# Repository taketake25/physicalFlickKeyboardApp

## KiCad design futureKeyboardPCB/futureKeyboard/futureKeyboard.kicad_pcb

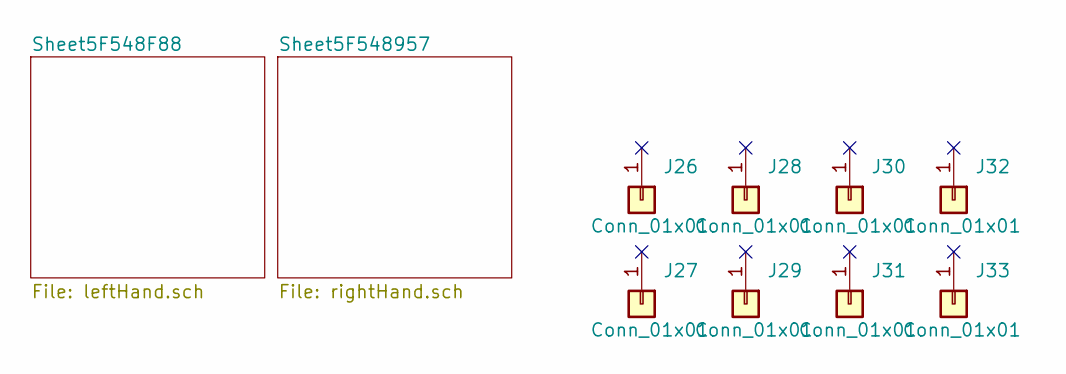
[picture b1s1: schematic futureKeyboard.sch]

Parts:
J26, J27, J28, J29, J30, J31, J32, J33: Conn_01x01; HOLE_3.2mm_nopad

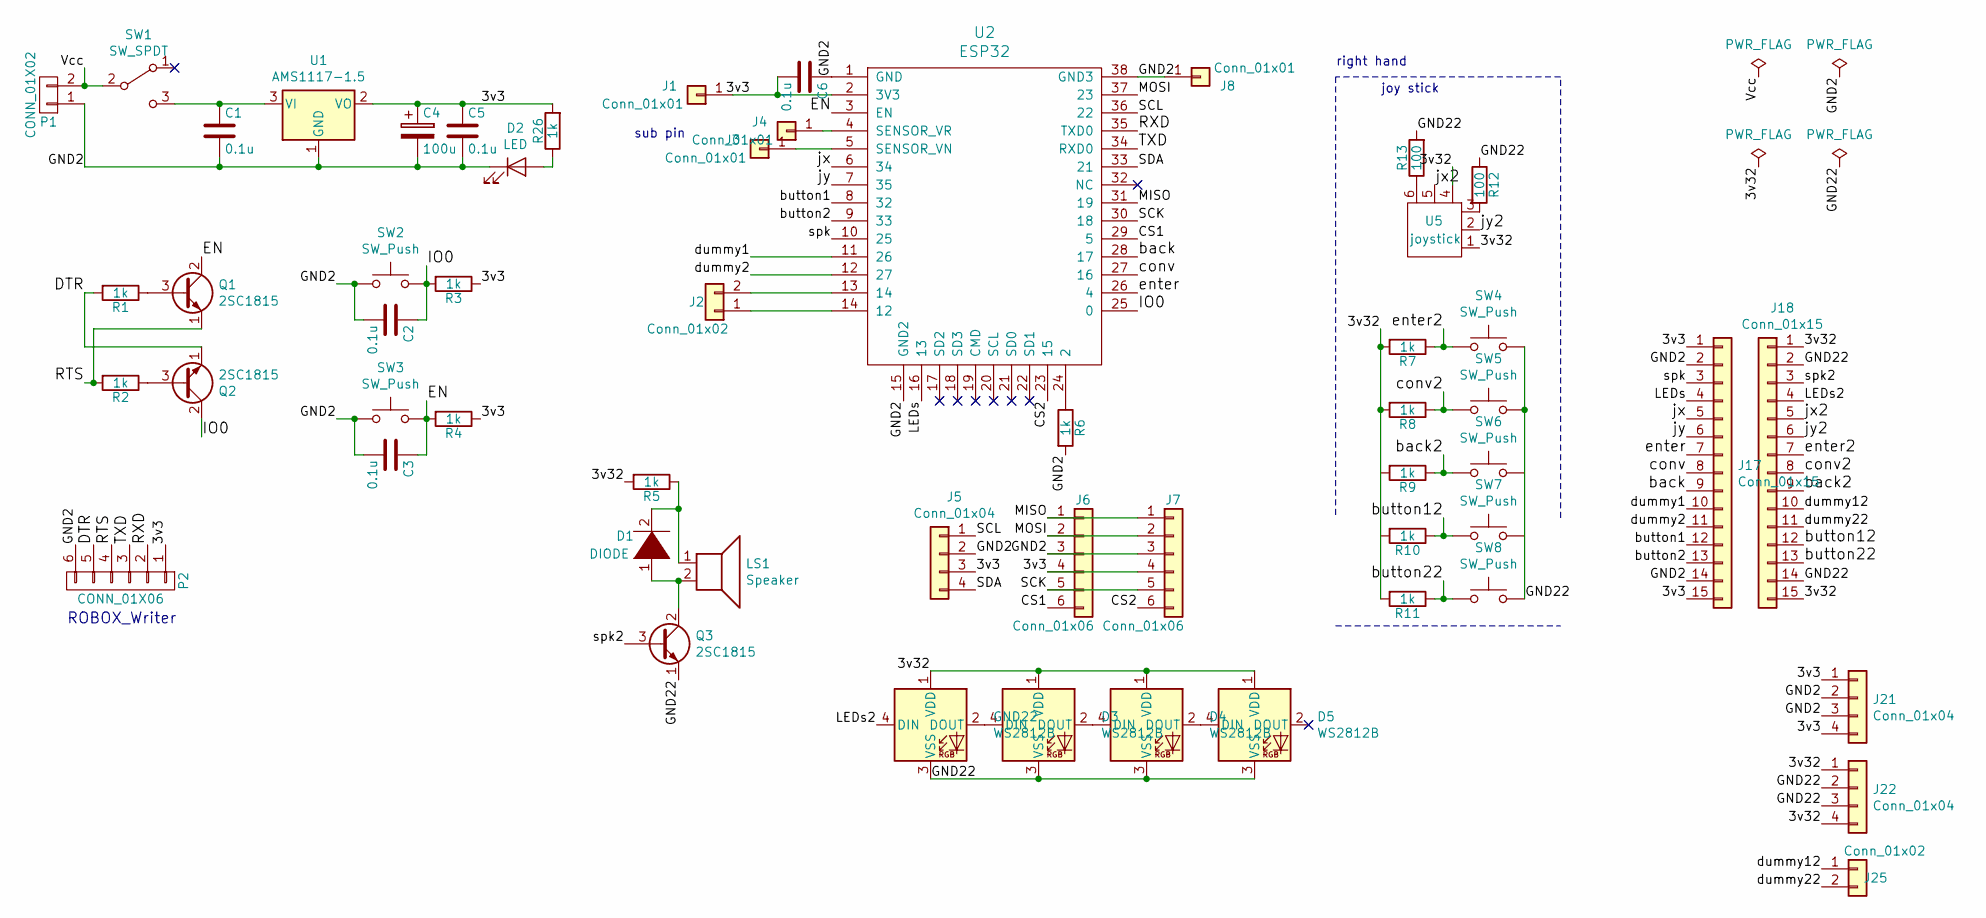
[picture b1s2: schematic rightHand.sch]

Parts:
C1, C2, C3, C5, C6: 0.1u; SMD-1608
C4: 100u; CP_Radial_D4.0mm_P2.00mm
D1: DIODE; D_A-405_P7.62mm_Horizontal
D2: LED; 2012LED
D3, D4, D5: WS2812B
GND22: WS2812B
J1, J3, J4, J8: Conn_01x01; PinHeader_1x01_P2.54mm_Vertical
J2, J25: Conn_01x02; PinHeader_1x02_P2.54mm_Vertical
J5: Conn_01x04; PinHeader_1x04_P2.54mm_Vertical
J6, J7: Conn_01x06; PinHeader_1x06_P2.54mm_Vertical
J17, J18: Conn_01x15; PinHeader_1x15_P2.54mm_Vertical_SMD_Pin1Left
J21, J22: Conn_01x04; PinHeader_1x04_P2.54mm_Vertical_SMD_Pin1Left
LS1: Speaker; small_speaker
P1: CONN_01X02; Connector_EH_2pin
P2: CONN_01X06; PinHeader_1x06_P2.54mm_Horizontal
Q1, Q2, Q3: 2SC1815; TO-92_Inline
R1, R2, R3, R4, R5, R6, R7, R8, R9, R10, R11, R26: 1k; SMD-1608
R12, R13: 100; SMD-1608
SW1: SW_SPDT; PinHeader_1x03_P2.54mm_Vertical
SW2, SW3, SW7, SW8: SW_Push; SMD_SW
SW4, SW5, SW6: SW_Push; SW_Cherry_MX_1.00u_PCB
U1: AMS1117-1.5; SOT-223-3_TabPin2
U2: ESP32; ESP-WROOM-32
U5: joystick; joyStick

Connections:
/Sheet5F548957/3v3: C4.1, C5.1, C6.2, J1.1, J5.3, J6.4, J7.4, J17.1, J17.15, J21.1, J21.4, P2.1, R3.1, R4.1, R26.2, U1.2 (VO), U2.2 (3V3)
/Sheet5F548957/3v32: D3.1 (VDD), D4.1 (VDD), D5.1 (VDD), GND22.1 (VDD), J18.1, J18.15, J22.1, J22.4, R5.2, R7.2, R8.2, R9.2, R10.2, R11.2, U5.1, U5.4
/Sheet5F548957/CS1: J6.6, U2.29 (5)
/Sheet5F548957/CS2: J7.6, U2.23 (15)
/Sheet5F548957/DTR: P2.5, Q2.1 (E), R1.2
/Sheet5F548957/EN: C3.1, Q1.2 (C), R4.2, SW3.2, U2.3 (EN)
/Sheet5F548957/GND2: C1.2, C2.2, C3.2, C4.2, C5.2, C6.1, D2.1 (K), J5.2, J6.3, J7.3, J8.1, J17.2, J17.14, J21.2, J21.3, P1.1, P2.6, R6.2, SW2.1, SW3.1, U1.1 (GND), U2.1 (GND), U2.15 (GND2), U2.38 (GND3)
/Sheet5F548957/GND22: D3.3 (VSS), D4.3 (VSS), D5.3 (VSS), GND22.3 (VSS), J18.2, J18.14, J22.2, J22.3, Q3.1 (E), R12.1, R13.2, SW4.2, SW5.2, SW6.2, SW7.2, SW8.2
/Sheet5F548957/IO0: C2.1, Q2.2 (C), R3.2, SW2.2, U2.25 (0)
/Sheet5F548957/LEDs: J17.4, U2.16 (13)
/Sheet5F548957/LEDs2: GND22.4 (DIN), J18.4
/Sheet5F548957/MISO: J6.1, J7.1, U2.31 (19)
/Sheet5F548957/MOSI: J6.2, J7.2, U2.37 (23)
/Sheet5F548957/RTS: P2.4, Q1.1 (E), R2.2
/Sheet5F548957/RXD: P2.2, U2.35 (TXD0)
/Sheet5F548957/SCK: J6.5, J7.5, U2.30 (18)
/Sheet5F548957/SCL: J5.1, U2.36 (22)
/Sheet5F548957/SDA: J5.4, U2.33 (21)
/Sheet5F548957/TXD: P2.3, U2.34 (RXD0)
/Sheet5F548957/Vcc: P1.2, SW1.2 (B)
/Sheet5F548957/back: J17.9, U2.28 (17)
/Sheet5F548957/back2: J18.9, R9.1, SW6.1
/Sheet5F548957/button1: J17.12, U2.8 (32)
/Sheet5F548957/button2: J17.13, U2.9 (33)
/Sheet5F548957/button12: J18.12, R10.1, SW7.1
/Sheet5F548957/button22: J18.13, R11.1, SW8.1
/Sheet5F548957/conv: J17.8, U2.27 (16)
/Sheet5F548957/conv2: J18.8, R8.1, SW5.1
/Sheet5F548957/dummy1: J17.10, U2.11 (26)
/Sheet5F548957/dummy2: J17.11, U2.12 (27)
/Sheet5F548957/dummy12: J18.10, J25.1
/Sheet5F548957/dummy22: J18.11, J25.2
/Sheet5F548957/enter: J17.7, U2.26 (4)
/Sheet5F548957/enter2: J18.7, R7.1, SW4.1
/Sheet5F548957/jx: J17.5, U2.6 (34)
/Sheet5F548957/jx2: J18.5, U5.5
/Sheet5F548957/jy: J17.6, U2.7 (35)
/Sheet5F548957/jy2: J18.6, U5.2
/Sheet5F548957/spk: J17.3, U2.10 (25)
/Sheet5F548957/spk2: J18.3, Q3.3 (B)
unnamed: C1.1, SW1.3 (C), U1.3 (VI)
unnamed: D1.1 (K), LS1.2, Q3.2 (C)
unnamed: D1.2 (A), LS1.1, R5.1
unnamed: D2.2 (A), R26.1
unnamed: D3.2 (DOUT), D4.4 (DIN)
unnamed: D3.4 (DIN), GND22.2 (DOUT)
unnamed: D4.2 (DOUT), D5.4 (DIN)
unnamed: J2.1, U2.14 (12)
unnamed: J2.2, U2.13 (14)
unnamed: J3.1, U2.5 (SENSOR_VN)
unnamed: J4.1, U2.4 (SENSOR_VR)
unnamed: Q1.3 (B), R1.1
unnamed: Q2.3 (B), R2.1
unnamed: R6.1, U2.24 (2)
unnamed: R12.2, U5.3
unnamed: R13.1, U5.6

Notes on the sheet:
joy stick
right hand
ROBOX_Writer
sub pin

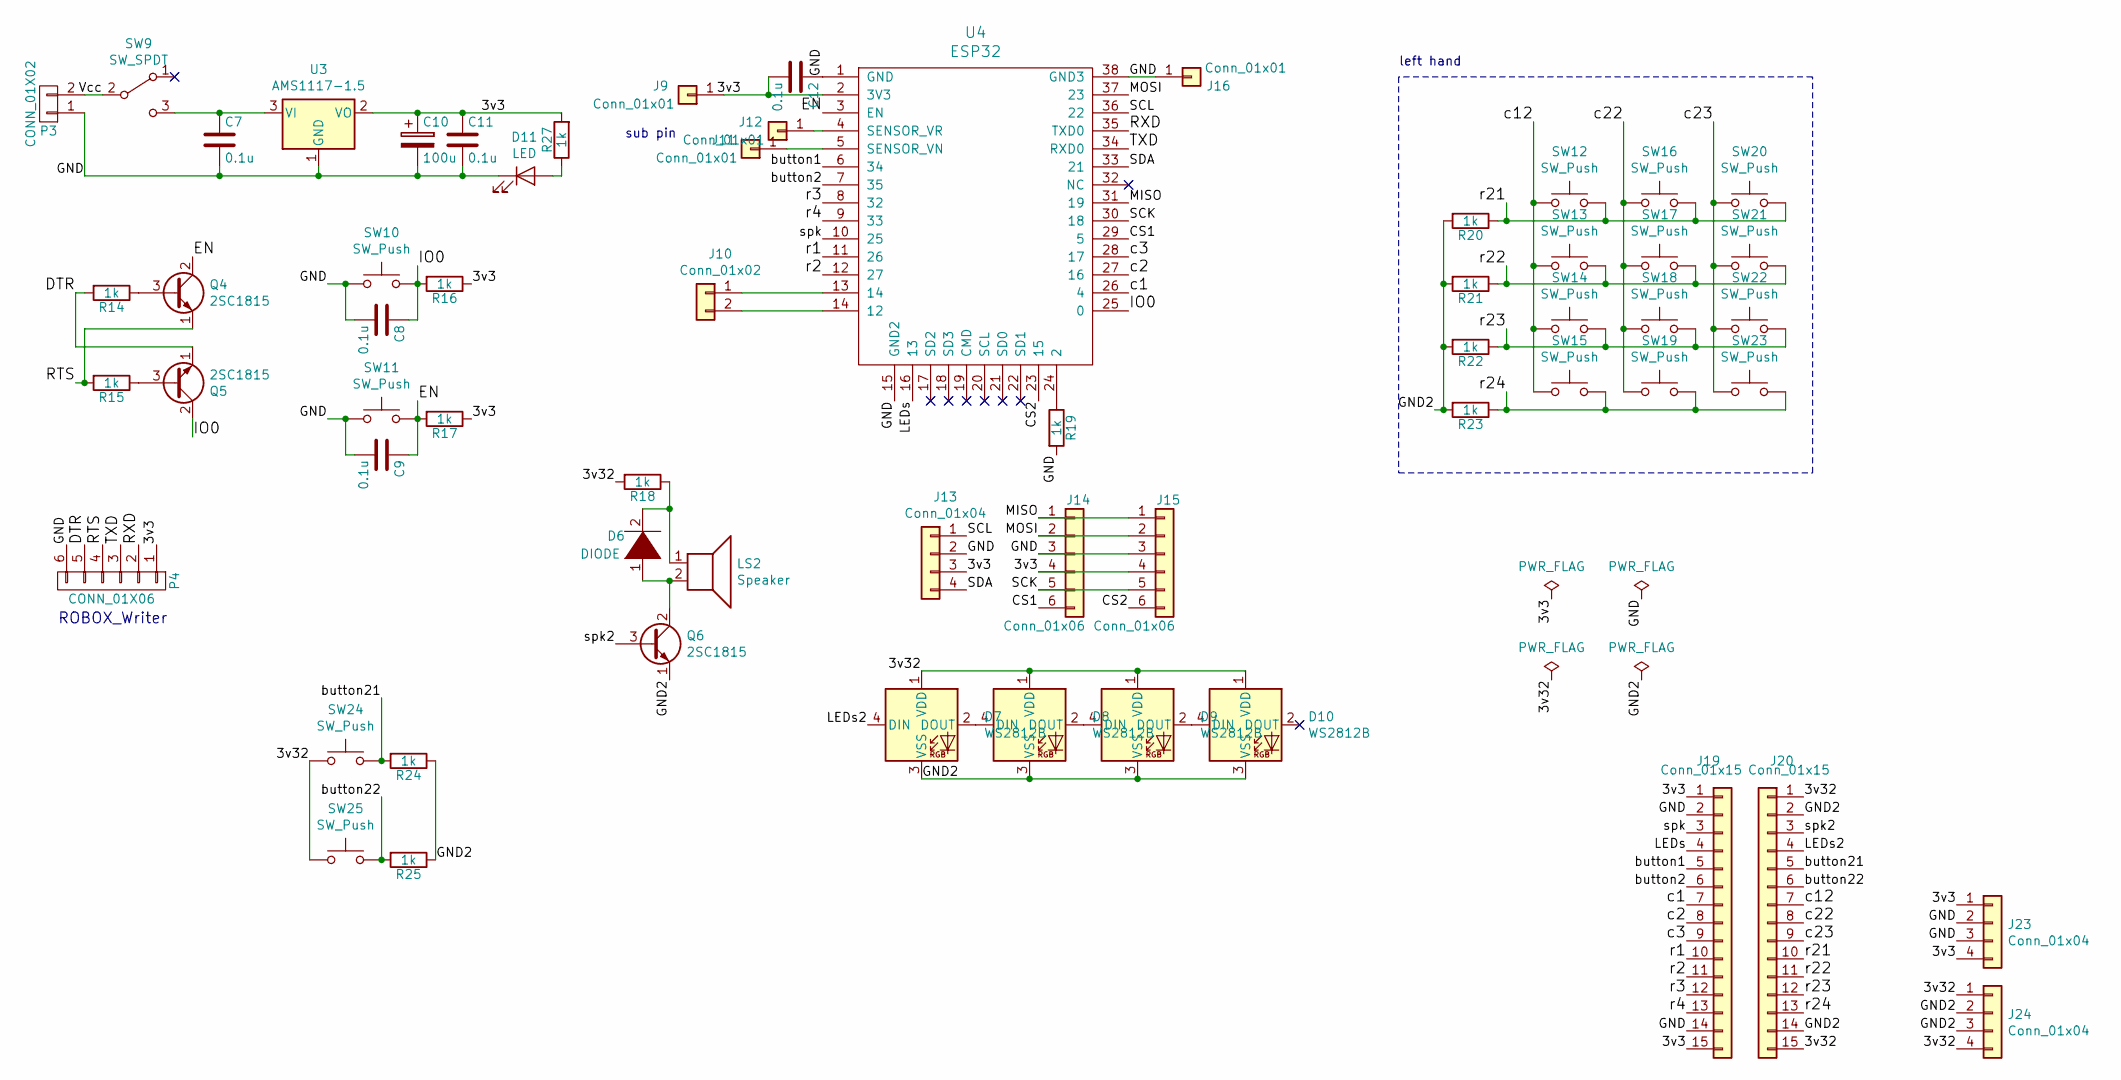
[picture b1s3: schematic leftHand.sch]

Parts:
C7, C8, C9, C11, C12: 0.1u; SMD-1608
C10: 100u; CP_Radial_D4.0mm_P2.00mm
D6: DIODE; D_A-405_P7.62mm_Horizontal
D7, D8, D9, D10: WS2812B
D11: LED; 2012LED
J9, J11, J12, J16: Conn_01x01; PinHeader_1x01_P2.54mm_Vertical
J10: Conn_01x02; PinHeader_1x02_P2.54mm_Vertical
J13: Conn_01x04; PinHeader_1x04_P2.54mm_Vertical
J14, J15: Conn_01x06; PinHeader_1x06_P2.54mm_Vertical
J19, J20: Conn_01x15; PinHeader_1x15_P2.54mm_Vertical_SMD_Pin1Left
J23, J24: Conn_01x04; PinHeader_1x04_P2.54mm_Vertical_SMD_Pin1Left
LS2: Speaker; small_speaker
P3: CONN_01X02; Connector_EH_2pin
P4: CONN_01X06; PinHeader_1x06_P2.54mm_Horizontal
Q4, Q5, Q6: 2SC1815; TO-92_Inline
R14, R15, R16, R17, R18, R19, R20, R21, R22, R23, R24, R25, R27: 1k; SMD-1608
SW9: SW_SPDT; PinHeader_1x03_P2.54mm_Vertical
SW10, SW11, SW24, SW25: SW_Push; SMD_SW
SW12, SW13, SW14, SW15, SW16, SW17, SW18, SW19, SW20, SW21, SW22, SW23: SW_Push; SW_Cherry_MX_1.00u_PCB
U3: AMS1117-1.5; SOT-223-3_TabPin2
U4: ESP32; ESP-WROOM-32

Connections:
/Sheet5F548F88/3v3: C10.1, C11.1, C12.2, J9.1, J13.3, J14.4, J15.4, J19.1, J19.15, J23.1, J23.4, P4.1, R16.1, R17.1, R27.2, U3.2 (VO), U4.2 (3V3)
/Sheet5F548F88/3v32: D7.1 (VDD), D8.1 (VDD), D9.1 (VDD), D10.1 (VDD), J20.1, J20.15, J24.1, J24.4, R18.2, SW24.1, SW25.1
/Sheet5F548F88/CS1: J14.6, U4.29 (5)
/Sheet5F548F88/CS2: J15.6, U4.23 (15)
/Sheet5F548F88/DTR: P4.5, Q5.1 (E), R14.2
/Sheet5F548F88/EN: C9.1, Q4.2 (C), R17.2, SW11.2, U4.3 (EN)
/Sheet5F548F88/GND: C7.2, C8.2, C9.2, C10.2, C11.2, C12.1, D11.1 (K), J13.2, J14.3, J15.3, J16.1, J19.2, J19.14, J23.2, J23.3, P3.1, P4.6, R19.2, SW10.1, SW11.1, U3.1 (GND), U4.1 (GND), U4.15 (GND2), U4.38 (GND3)
/Sheet5F548F88/GND2: D7.3 (VSS), D8.3 (VSS), D9.3 (VSS), D10.3 (VSS), J20.2, J20.14, J24.2, J24.3, Q6.1 (E), R20.2, R21.2, R22.2, R23.2, R24.1, R25.1
/Sheet5F548F88/IO0: C8.1, Q5.2 (C), R16.2, SW10.2, U4.25 (0)
/Sheet5F548F88/LEDs: J19.4, U4.16 (13)
/Sheet5F548F88/LEDs2: D7.4 (DIN), J20.4
/Sheet5F548F88/MISO: J14.1, J15.1, U4.31 (19)
/Sheet5F548F88/MOSI: J14.2, J15.2, U4.37 (23)
/Sheet5F548F88/RTS: P4.4, Q4.1 (E), R15.2
/Sheet5F548F88/RXD: P4.2, U4.35 (TXD0)
/Sheet5F548F88/SCK: J14.5, J15.5, U4.30 (18)
/Sheet5F548F88/SCL: J13.1, U4.36 (22)
/Sheet5F548F88/SDA: J13.4, U4.33 (21)
/Sheet5F548F88/TXD: P4.3, U4.34 (RXD0)
/Sheet5F548F88/Vcc: P3.2, SW9.2 (B)
/Sheet5F548F88/button1: J19.5, U4.6 (34)
/Sheet5F548F88/button2: J19.6, U4.7 (35)
/Sheet5F548F88/button21: J20.5, R24.2, SW24.2
/Sheet5F548F88/button22: J20.6, R25.2, SW25.2
/Sheet5F548F88/c1: J19.7, U4.26 (4)
/Sheet5F548F88/c2: J19.8, U4.27 (16)
/Sheet5F548F88/c3: J19.9, U4.28 (17)
/Sheet5F548F88/c12: J20.7, SW12.1, SW13.1, SW14.1, SW15.1
/Sheet5F548F88/c22: J20.8, SW16.1, SW17.1, SW18.1, SW19.1
/Sheet5F548F88/c23: J20.9, SW20.1, SW21.1, SW22.1, SW23.1
/Sheet5F548F88/r1: J19.10, U4.11 (26)
/Sheet5F548F88/r2: J19.11, U4.12 (27)
/Sheet5F548F88/r3: J19.12, U4.8 (32)
/Sheet5F548F88/r4: J19.13, U4.9 (33)
/Sheet5F548F88/r21: J20.10, R20.1, SW12.2, SW16.2, SW20.2
/Sheet5F548F88/r22: J20.11, R21.1, SW13.2, SW17.2, SW21.2
/Sheet5F548F88/r23: J20.12, R22.1, SW14.2, SW18.2, SW22.2
/Sheet5F548F88/r24: J20.13, R23.1, SW15.2, SW19.2, SW23.2
/Sheet5F548F88/spk: J19.3, U4.10 (25)
/Sheet5F548F88/spk2: J20.3, Q6.3 (B)
unnamed: C7.1, SW9.3 (C), U3.3 (VI)
unnamed: D6.1 (K), LS2.2, Q6.2 (C)
unnamed: D6.2 (A), LS2.1, R18.1
unnamed: D7.2 (DOUT), D8.4 (DIN)
unnamed: D8.2 (DOUT), D9.4 (DIN)
unnamed: D9.2 (DOUT), D10.4 (DIN)
unnamed: D11.2 (A), R27.1
unnamed: J10.1, U4.13 (14)
unnamed: J10.2, U4.14 (12)
unnamed: J11.1, U4.5 (SENSOR_VN)
unnamed: J12.1, U4.4 (SENSOR_VR)
unnamed: Q4.3 (B), R14.1
unnamed: Q5.3 (B), R15.1
unnamed: R19.1, U4.24 (2)

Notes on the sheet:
left hand
ROBOX_Writer
sub pin

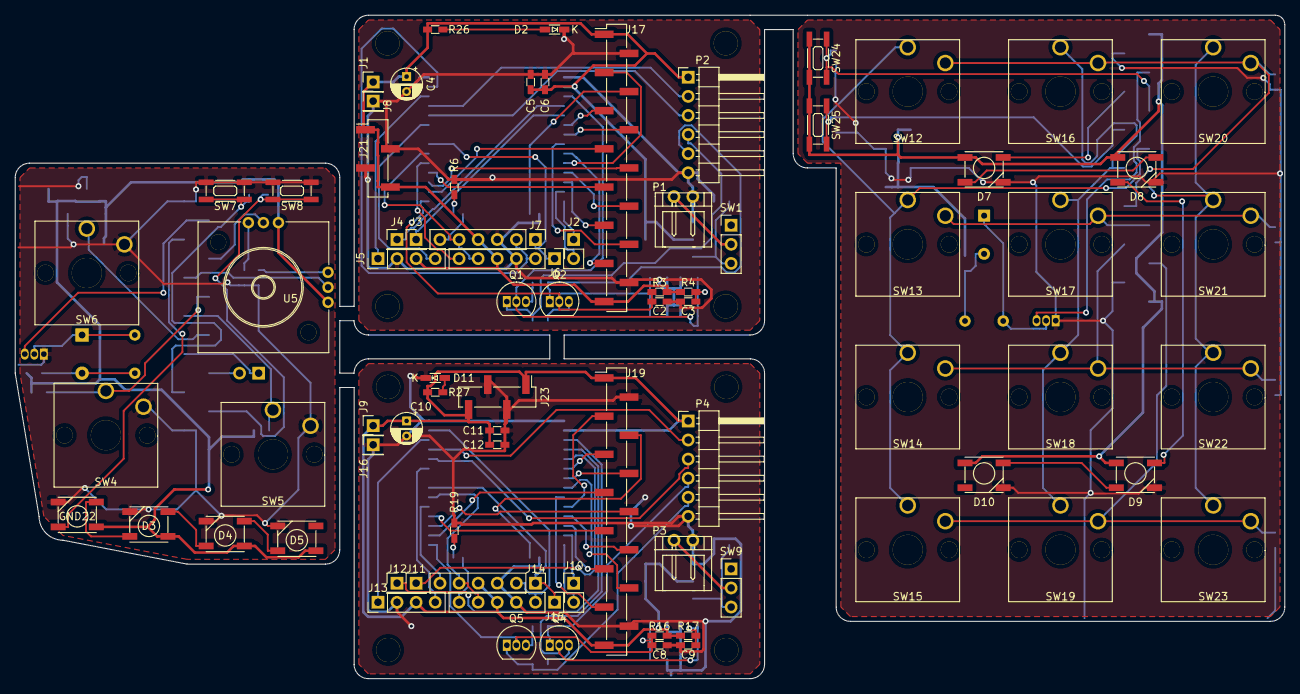
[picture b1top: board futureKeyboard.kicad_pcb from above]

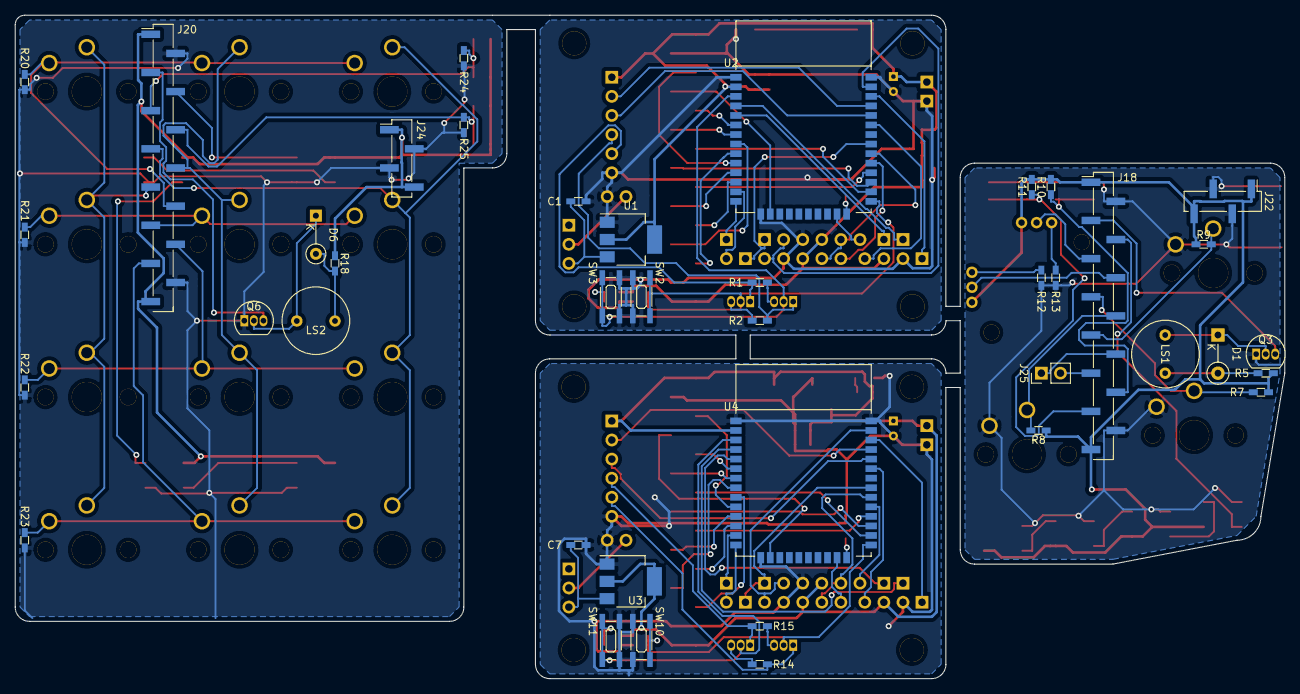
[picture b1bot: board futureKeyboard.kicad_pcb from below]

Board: 2 copper layers, 168.9 x 88.3 mm, 126 parts (40 on the bottom side), 110 nets.

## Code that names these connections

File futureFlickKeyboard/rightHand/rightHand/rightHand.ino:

#include <WiFi.h>
#include <esp_now.h>
#include <Adafruit_NeoPixel.h>
#include "BluetoothSerial.h"

#define LEDs 13
#define button1 32
#define button2 33
#define spk 25
#define enter 16
#define conv 17
#define back 4
#define jx 34
#define jy 35
#define pi 3.141592
#define CHANNEL 0

/* full color LED definition */
#ifdef __AVR__
#include <avr/power.h> // Required for 16 MHz Adafruit Trinket
#endif
#define NUMPIXELS 4 // Popular NeoPixel ring size
Adafruit_NeoPixel pixels(NUMPIXELS, LEDs, NEO_GRB + NEO_KHZ800);

BluetoothSerial SerialBT;

int lines[4]={0};
char w[2]={0};
char beforew[2]={0};
int key = 0;


// Init ESP Now with fallback
void InitESPNow() {
  WiFi.disconnect();
  if (esp_now_init() == ESP_OK) {
    Serial.println("ESPNow Init Success");
  }
  else {
    Serial.println("ESPNow Init Failed");
    ESP.restart();
  }
}

// config AP SSID
void configDeviceAP() {
  const char *SSID = "Slave_rightHand";
  bool result = WiFi.softAP(SSID, "ffkb_rightHand", CHANNEL, 0);
  if (!result) {
    Serial.println("AP Config failed.");
  } else {
    Serial.println("AP Config Success. Broadcasting with AP: " + String(SSID));
  }
}

// callback when data is recv from Master
void OnDataRecv(const uint8_t *mac_addr, const uint8_t *data, int data_len) {
  char macStr[18];
  snprintf(macStr, sizeof(macStr), "%02x:%02x:%02x:%02x:%02x:%02x",
           mac_addr[0], mac_addr[1], mac_addr[2], mac_addr[3], mac_addr[4], mac_addr[5]);
  Serial.print("Last Packet Recv from: "); Serial.println(macStr);
  Serial.print("Last Packet Recv Data: "); Serial.println(*data);
  Serial.println("");

  key = *data;
//  Serial.print("key:");

}


// ↑ ESP-NOW       ---------------------------------------------------------------------
// ↓ Original Code ---------------------------------------------------------------------


void setup() {
  Serial.begin(115200);
  SerialBT.begin("Future Flick Keyboard v0");

  pinMode(jx,INPUT); //ジョイスティック
  pinMode(jy,INPUT);
  pinMode(button1,INPUT);
  pinMode(button2,INPUT);
  pinMode(back,INPUT); // 消す
  pinMode(enter,INPUT); // 改行 or あ列
  pinMode(conv,INPUT); //スペース


  WiFi.mode(WIFI_AP);
  configDeviceAP();  // configure device AP mode
  Serial.print("AP MAC: "); Serial.println(WiFi.softAPmacAddress());  // This is the mac address of the Slave in AP Mode
  InitESPNow();  // Init ESPNow with a fallback logic
  esp_now_register_recv_cb(OnDataRecv);  // Once ESPNow is successfully Init, we will register for recv CB to get recv packer info.


  /* full color LED init */
  #if defined(__AVR_ATtiny85__) && (F_CPU == 16000000) // for setup full color LEDs
    clock_prescale_set(clock_div_1);
  #endif
  pixels.begin();
  pixels.clear(); // Set all pixel colors to 'off'
  pixels.setPixelColor(0, pixels.Color(255, 0, 0));
  pixels.setPixelColor(1, pixels.Color(0, 255, 0));
  pixels.setPixelColor(2, pixels.Color(0, 0, 255));
  pixels.setPixelColor(3, pixels.Color(255, 255, 255));
  pixels.show();
  delay(1000);
//  pixels.clear(); // Set all pixel colors to 'off'
//  pixels.show();


  w[0]=0; w[1]=0; // 入力内容を初期化  
  key=0;
}


void loop() {
  
  memset(lines,0,sizeof(lines[0])*4);
  //どのボタンが押されているかを認識し、keyに1~12の値として入力

//  Serial.print(digitalRead(enter));  Serial.print("  ");
//  Serial.print(analogRead(jx));  Serial.print("  ");
//  Serial.print(analogRead(jy));  Serial.println("  ");
  printKey(key);

  delay(50); 
}


void printKey(int key){ // 入力キーをinput
  int x = analogRead(jx); // ジョイスティックの値を取得（0~4095）
  int y = analogRead(jy);
  bool output = false;

  int wordIndex = 0;

  if(key!=0){ // 左手側が入力されているとき
    if(sqrt((x-2048)*(x-2048) + (y-2048)*(y-2048)) > 1250){ // ジョイスティックがある一定以上傾いていたとき（値の範囲に注意）
      float direc = (2.0*(atan2(2048-y,2048-x)+0.785398))/pi; // ジョイスティックの角度を求め、45度ごとに値が1ずつ変化するように変換（値の範囲に注意）

//      Serial.print(atan2(2048-y,2048-x)+0.785398);
      if(direc>=0){ // ジョイスティックの上側
        switch((int)direc){
          case 0:  Serial.print("<-"); w[1]='i'; wordIndex = 1; break; // ←
          case 1:  Serial.print("!"); w[1]='o'; wordIndex = 4; break; // ↓
          default:  Serial.print("->"); w[1]='e'; wordIndex = 3; break; // →
        }
        output = true;
      }else{ // ジョイスティックの下側（-1以上0未満の値がintにした際に0になっちゃうので）
        switch((int)direc){
          case -1: Serial.print("->"); w[1]='e'; wordIndex = 3; break; // →
          default: Serial.print("i"); w[1]='u'; wordIndex = 2; break; // ↑
        }
        output = true;
      }

    }else if(!digitalRead(enter)){ // フリックしない文字（あ行）はEnterキーで入力
      Serial.print("*");
      w[1]='a'; 
      wordIndex = 0; 
      output = true;
    }else{
      w[1]=0;
    }

    switch(key){
      case 1:w[0]=w[1];w[1]=0;break; //とりあえずESCを入力している
      case 2:w[0]='k';break;
      case 3:w[0]='s';break;
      case 4:w[0]='t';break;
      case 5:w[0]='n';break;
      case 6:w[0]='h';break;
      case 7:w[0]='m';break;
      case 8:w[0]='y';break;
      case 9:w[0]='r';break;
      case 10:w[0]=' ';break;
      case 11:w[0]='w';break;
      case 12:w[0]=' ';break;
    }
    wordIndex += (key-1)*5; // 左手の入力値を代入する

    if(w[0]=='w'){ // ワ行のみ入力が変化
      if(w[1]=='i') w[1]='o';
      if(w[1]=='u') {w[0]=w[1]='n';}
      if(w[1]=='e') {w[0]='-'; w[1]=0x1b;}
    }

    // 出力
    if(output && (beforew[0]!=w[0] || beforew[1]!=w[1])) {SerialBT.print(wordIndex); Serial.println(wordIndex);} // 連続入力を避ける
  }else { // 左手側が入力されていないとき
    if(!digitalRead(enter)) {w[0]='\n'; w[1]='a';wordIndex=60; output=true;} // Enter長押し時に、改行されてしまう問題があるため、w[1]='a'を入れる糞コード
    else if(!digitalRead(back)) {/*lcd.fillScreen(0x000000);*/  /*lcd.setCursor(0, 0);*/} // 画面をクリア
    else if(!digitalRead(conv)) {w[0]=' '; w[1]='a';wordIndex=61; output=true;} // スペースを空ける
    else {w[0]=0;}
    if(output && (beforew[0]!=w[0] && beforew[1]!=w[1])) {SerialBT.print(wordIndex); Serial.print(wordIndex);} // 連続入力を避ける
//    if(beforew[0]!=w[0] && beforew[1]!=w[1]) {lcd.printf("%c",w[0]); SerialBT.print(w[0]); /*SerialBT.print("あ");*/} // 連続入力を避ける
  }

  beforew[0]=w[0]; // 前回の入力を記憶（長押しで同じ文字が入力されいないようにする）
  beforew[1]=w[1];

}

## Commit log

2020-09-02 add unfinished PCB data
2020-09-02 add right hand circuit on .sch file
2020-09-02 add left hand circuit on .sch file
2020-09-02 create net list
2020-09-02 fix netlist, and make PCB file
2020-09-02 divide layors, make footprints, aligned footprints
2020-09-02 change layer connecter to be same pins total
2020-09-03 fix circuit bags, and placement electric parts
2020-09-03 complete placement electronic parts
2020-09-03 complete footprint placement
2020-09-03 complete PCB
2020-09-04 add Logo
2020-09-04 output two kinds of garber files
2020-09-08 fix arduino program
2020-10-15 add arduino project using esp-now, new PCB
2020-10-16 update arduino programs
2020-11-01 fixed amount of the source codes
2020-11-01 add 3D datas of the case
2020-11-02 fixed bugs of input in smartphones
2021-07-05 Create LICENSE
